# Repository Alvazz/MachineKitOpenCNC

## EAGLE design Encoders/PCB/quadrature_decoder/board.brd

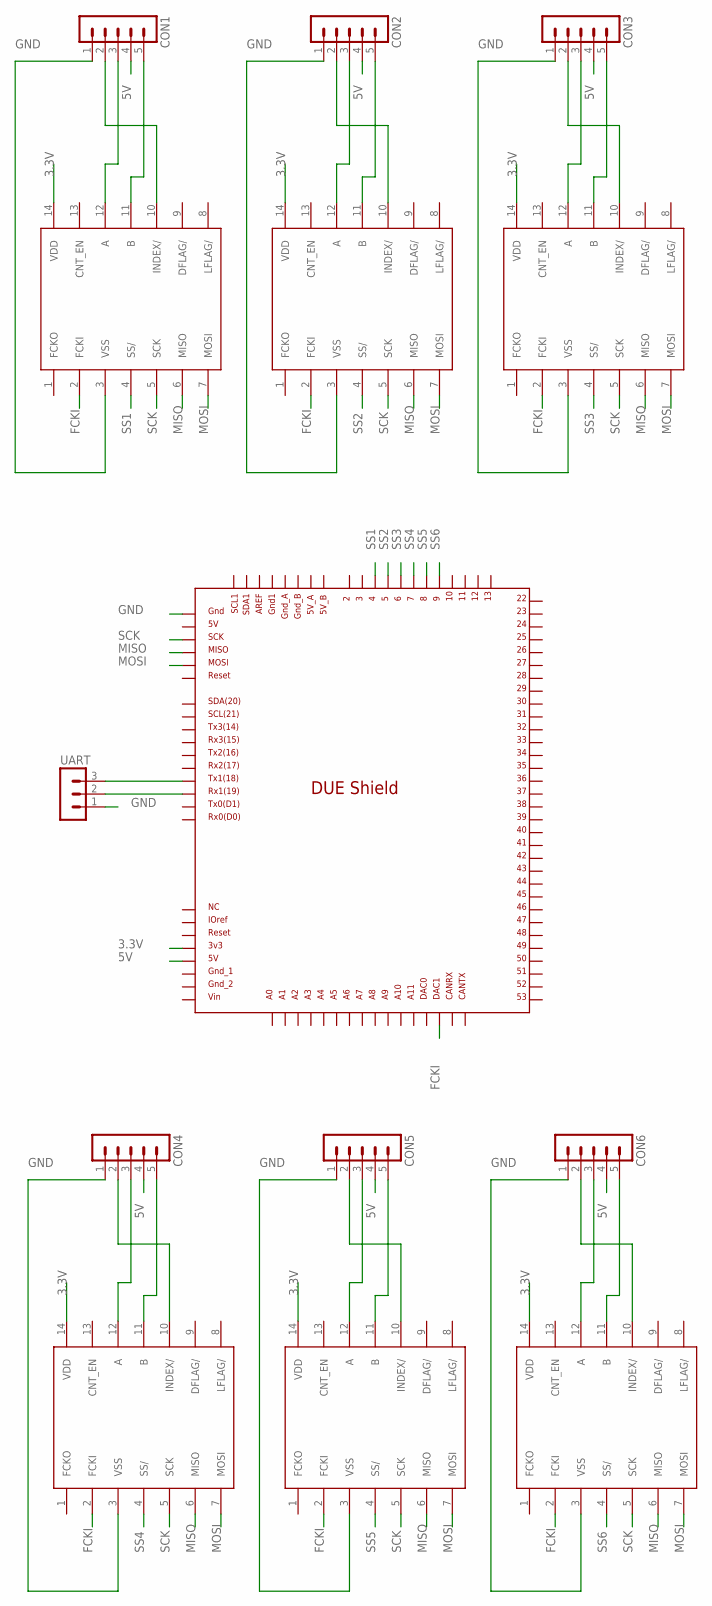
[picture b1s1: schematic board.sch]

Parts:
CON1, CON2, CON3: MA05-1
CON4, CON5, CON6: MA05-1(BOTTOM)
IC1, IC2, IC3, IC4, IC5, IC6: LFLS7366R; SO14
U$1: DUE(ENCODER)
UART: MA03-1

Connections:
3.3V: IC1.14 (VDD), IC2.14 (VDD), IC3.14 (VDD), IC4.14 (VDD), IC5.14 (VDD), IC6.14 (VDD), U$1.3V3
5V: CON1.4, CON2.4, CON3.4, CON4.4, CON5.4, CON6.4, U$1.5V
FCKI: IC1.2 (FCKI), IC2.2 (FCKI), IC3.2 (FCKI), IC4.2 (FCKI), IC5.2 (FCKI), IC6.2 (FCKI), U$1.DAC1
GND: CON1.1, CON2.1, CON3.1, CON4.1, CON5.1, CON6.1, IC1.3 (VSS), IC2.3 (VSS), IC3.3 (VSS), IC4.3 (VSS), IC5.3 (VSS), IC6.3 (VSS), U$1.5V_ICSP, UART.1
MISO: IC1.6 (MISO), IC2.6 (MISO), IC3.6 (MISO), IC4.6 (MISO), IC5.6 (MISO), IC6.6 (MISO), U$1.MISO_ICSP
MOSI: IC1.7 (MOSI), IC2.7 (MOSI), IC3.7 (MOSI), IC4.7 (MOSI), IC5.7 (MOSI), IC6.7 (MOSI), U$1.MOSI_ICSP
unnamed: CON2.2, IC2.10 (INDEX/)
unnamed: U$1.TX1, UART.3
unnamed: U$1.RX1, UART.2
unnamed: CON2.3, IC2.12 (A)
unnamed: CON2.5, IC2.11 (B)
unnamed: CON3.2, IC3.10 (INDEX/)
unnamed: CON3.3, IC3.12 (A)
unnamed: CON3.5, IC3.11 (B)
unnamed: CON1.2, IC1.10 (INDEX/)
unnamed: CON1.3, IC1.12 (A)
unnamed: CON1.5, IC1.11 (B)
unnamed: CON5.2, IC5.10 (INDEX/)
unnamed: CON5.3, IC5.12 (A)
unnamed: CON5.5, IC5.11 (B)
unnamed: CON6.2, IC6.10 (INDEX/)
unnamed: CON6.3, IC6.12 (A)
unnamed: CON6.5, IC6.11 (B)
unnamed: CON4.2, IC4.10 (INDEX/)
unnamed: CON4.3, IC4.12 (A)
unnamed: CON4.5, IC4.11 (B)
SCK: IC1.5 (SCK), IC2.5 (SCK), IC3.5 (SCK), IC4.5 (SCK), IC5.5 (SCK), IC6.5 (SCK), U$1.SCK_ICSP
SS1: IC1.4 (SS/), U$1.4
SS2: IC2.4 (SS/), U$1.5
SS3: IC3.4 (SS/), U$1.6
SS4: IC4.4 (SS/), U$1.7
SS5: IC5.4 (SS/), U$1.8
SS6: IC6.4 (SS/), U$1.9

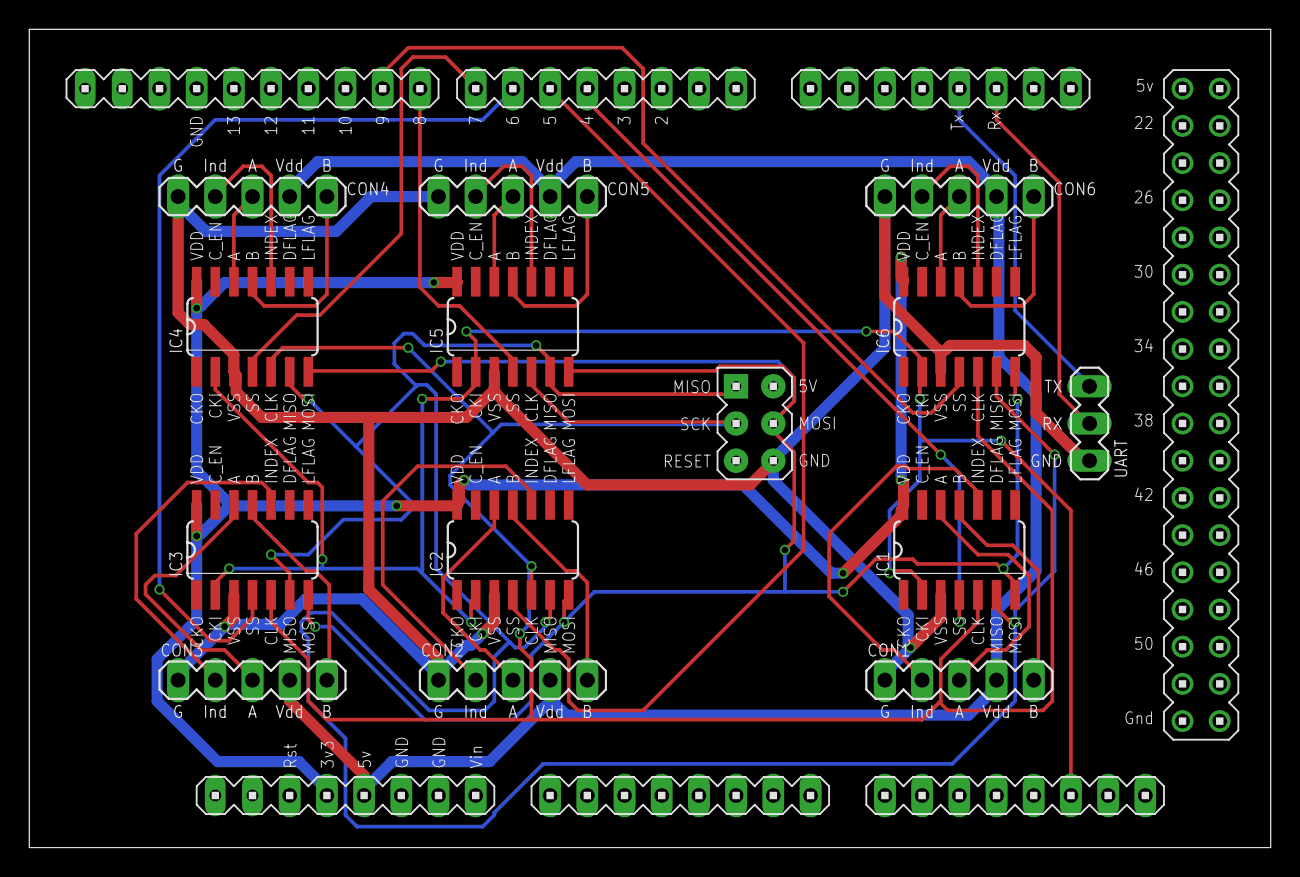
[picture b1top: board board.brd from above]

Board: 2 copper layers, 84.8 x 55.9 mm, 14 parts (0 on the bottom side), 33 nets.

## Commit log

2017-10-19 initial push
    initial counter code for arduino due.
    using pwm to generate fcki for the counter chip;
2017-10-24 add python folder
2017-10-24 Bring in python bokeh code
2017-10-24 updated arduino code
2017-10-25 update arduino code
    - updated initSpi function to have multple SPIs as inputs
    - unified function naming style
    - changed "initCounter" to "setCounter" and added another "initCounter" function to initialize the registers
2017-10-25 update arduino code
    - moved definitions and functions to counter.h file
    - changed "unsigned long" to "uint32_t"
    - "atoi" to "strtoul"
2017-10-25 capitalization consistency :-)
2017-10-25 start stateData struct
2017-10-27 add timer setup
    install DueTimer library in arduino ide
2017-10-29 add arduino due pcb outline
2017-10-30 mechanical
2017-10-30 updated mechanical
2017-10-30 updated frame
2017-11-02 new eagle files
2017-11-02 board
2017-11-10 deleted temp eagle files
2017-11-10 Revert "deleted temp eagle files"
    This reverts commit 96ff2f756feb4d77b0f38149fa13669738a3dee2.
2017-11-15 new board layout
2017-11-16 new board
2017-11-16 another board
2017-11-20 update arduino code
2017-11-21 pncComm changes
2017-11-30 pncComm updates
2017-12-05 modularizing
2017-12-07 added hotend control
    control is the pid controller
    control1 is the proportional on measurement pid controller.
    serialPlot plots both temperature and duty cycle.
2017-12-16 updated temp control code.
2017-12-20 broke pncApp
2017-12-22 fixed control
2018-01-03 SP integration working
2018-01-12 code updates
2018-01-19 added FDM tool holder
2018-01-22 new boards and stuff
2018-01-22 added rule file for eagle
2018-01-22 changed pcb libs.
2018-01-23 rerouted
2018-01-23 updated board
2018-01-26 added axis offsets
2018-01-30 update offsets
2018-02-14 fixed encoders
2018-02-15 updated PCB board and tool holder CAD model
2018-03-05 updated the frame for pocketnc
2018-03-06 pycharm and motor mounts
2018-03-06 pycharm
2018-03-06 motor mounts
2018-03-09 added odrive code
2018-03-12 updated Frame for PocketNC
    Changed the thickness of the bracket and corresponding screw holes.
2018-03-14 testing submodules
2018-03-14 new shelf, hw configs, etc
2018-03-16 mechanical updates
2018-03-21 added serial
2018-03-24 serial fixes
2018-03-26 working encoder integration to SP
2018-03-26 working SP control
2018-03-28 trapezoidal trajectory planner
2018-03-29 TP updates
2018-04-12 added TCP feedback parsing
2018-04-18 bug fixes, etc
2018-04-24 updates to SP integration
2018-05-11 thread safety, motion queues, etc etc
2018-05-16 binary feedback
2018-05-21 SP user functions and other changes
2018-05-25 better binary/ascii FB/control handoffs, etc
2018-06-01 total refactor of feedback decoding logic, implementation of DataStoreManager push/pull methods
2018-06-01 per axis encoder IC setting
2018-06-01 added ability to set individual IC registers, major refactor of command handler, plus better data storage in structures
2018-06-01 added bandwidth setting for encoder board from UART link
2018-06-02 refactor python serial code
2018-06-03 added binary data transmission from decoder board, plus reception in python
2018-06-04 encoder data pushing into DB, pulling by readMachine(1)
2018-06-07 beginnings of multiprocessing port, does not run :100:
2018-06-09 close to working multiprocessing version :smoking:
2018-06-10 most of the bugs worked out of multiprocessing port, SP can now launch processes too
2018-06-14 substantially improved SP integraion, most function calls work from python. Also improved startup/shotdown from SP
2018-06-24 beginnings of websocket implrmentation, switching to websockets instead of websocket-client
2018-06-25 working startup with python.exe, bug fixes in buffer level feedback parsing, changes to websocket logic
2018-06-28 SP interface now runs on loopback socket
2018-06-29 socket comms working pretty well for once
2018-07-02 Fixed mergeSort, more general approach to data integration with SP socket (that took forever to write)
2018-07-02 some bugfixes and organization. Working release
2018-07-09 fixed encoder calibration, working on network PID
2018-07-09 fixed encoder baudrate bug, beware of axis 5 encoder set
2018-07-10 pretty reliable now, starting motion_queue_feeder implementation, wish me luck
2018-07-11 holy shit this one actually works
2018-07-17 fixed some mess with time sync, working version for demo video
2018-07-20 almost working execution of points from websocket
2018-07-21 major websocket changes, working well with subsequences
2018-07-23 major websocket update, control updates
2018-07-24 odrive integration, move odrive interface and encoder interface to separate threads in deviceInterface process
2018-07-29 working error recovery and re-execution of already planned trajectories
2018-07-30 rapids planned on mukulLab, still haven't ordered encoders...
2018-08-09 working rapids from TP
2018-08-17 updates to rapid/SP_traj state handling
2018-08-28 encoder plate and cooling duct
2018-09-06 mechanical updates in progress
2018-09-06 test commit
2018-09-17 more mechanical updates
2018-09-25 More power shelf updates
2018-09-30 shelf assembly, adding bolt pattern for converters
2018-10-01 starting integration of SP control
2018-10-17 mechanical changes
2018-10-19 implementing control machine from SP
2018-10-23 more work on control from SP
2018-10-25 updates to websocket interface, new electronics shelving
2018-11-01 mechanical and websocket updates
2018-11-05 updates to websocket interface
2018-11-13 websocket packetizing updates, etc
2018-11-15 websocket bug fixes, drive shelf updates
2018-11-17 changes to websocket sequence splicing implementation
2018-11-17 seemingly working version with control/feedback using websocket threads
2018-11-19 full run, websocket in separate process now
2018-11-21 integrated with SP, working database archiving
2018-12-03 more updates?
2018-12-07 added ability to halt and restart motion
2018-12-11 additional spindle integration, data export
2018-12-14 version used for data collection
2018-12-29 testing scripps
2018-12-29 analysis scripts, etc
2018-12-29 Revert "analysis scripts, etc"
    This reverts commit 1feb4f571a0a97d1137a908c46c3a2ef4a017a5f.
2018-12-29 analysis scripps again
2019-01-07 analysis changes
2019-01-07 matlab code changes
2019-01-07 workspace?
2019-01-07 ignore settings
2019-01-08 trying to fix module import
2019-01-08 and another quick fix to that
2019-01-08 more import fixes
2019-01-08 again
2019-01-08 file copying changes
2019-01-08 some cross platform changes
2019-01-08 more cross platform changes, working with new fast read SP version
2019-01-08 spindle integration
2019-01-11 updates to storage of multipolyline transmissions
